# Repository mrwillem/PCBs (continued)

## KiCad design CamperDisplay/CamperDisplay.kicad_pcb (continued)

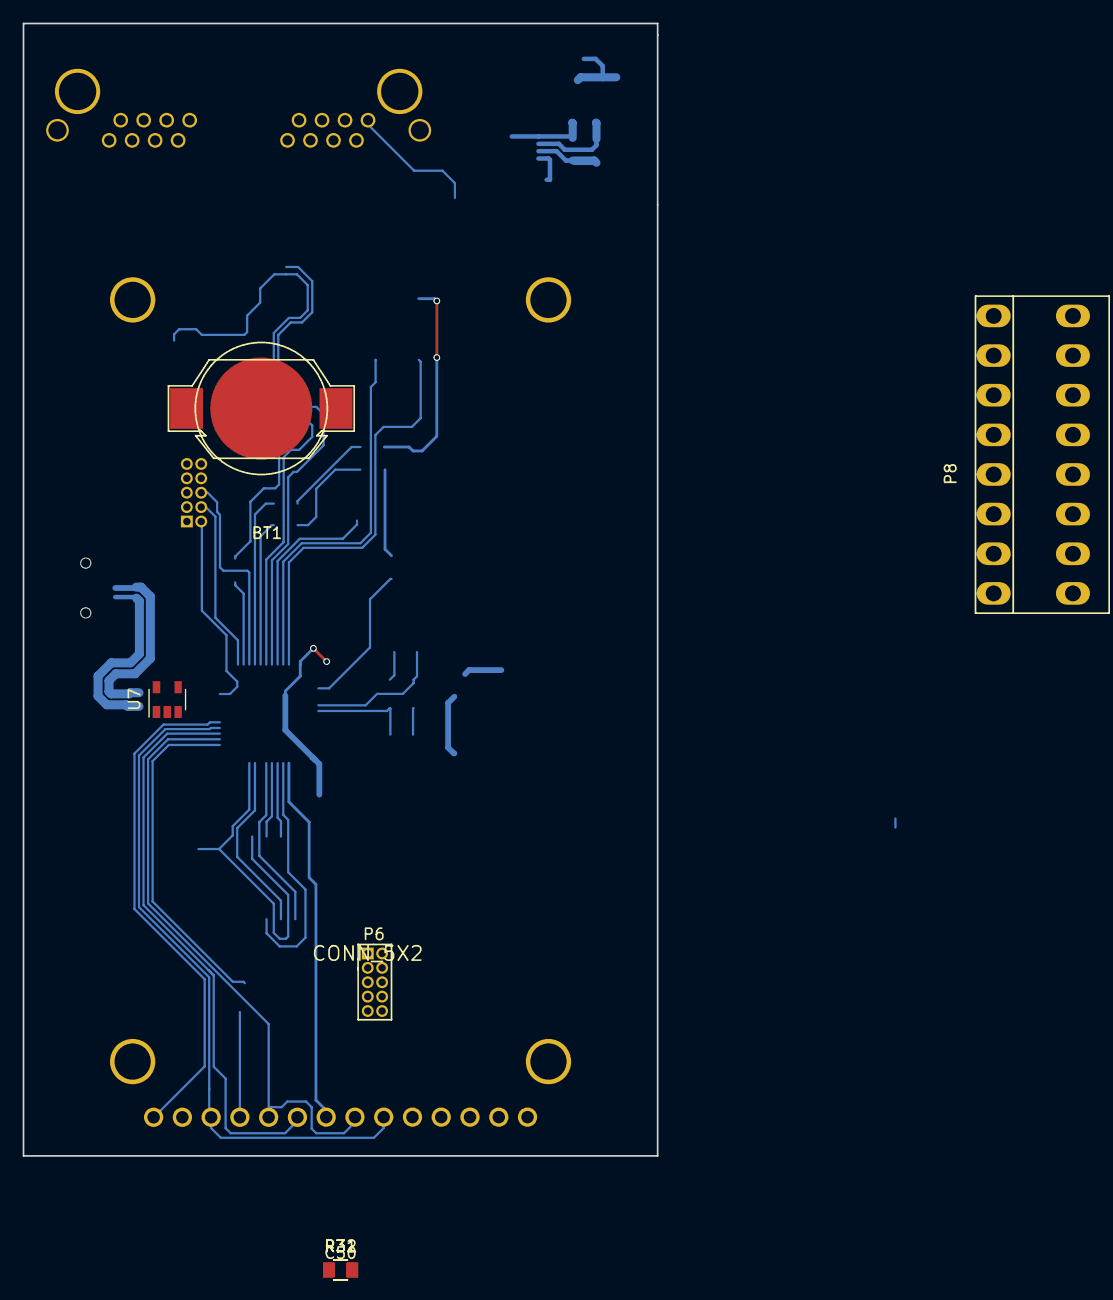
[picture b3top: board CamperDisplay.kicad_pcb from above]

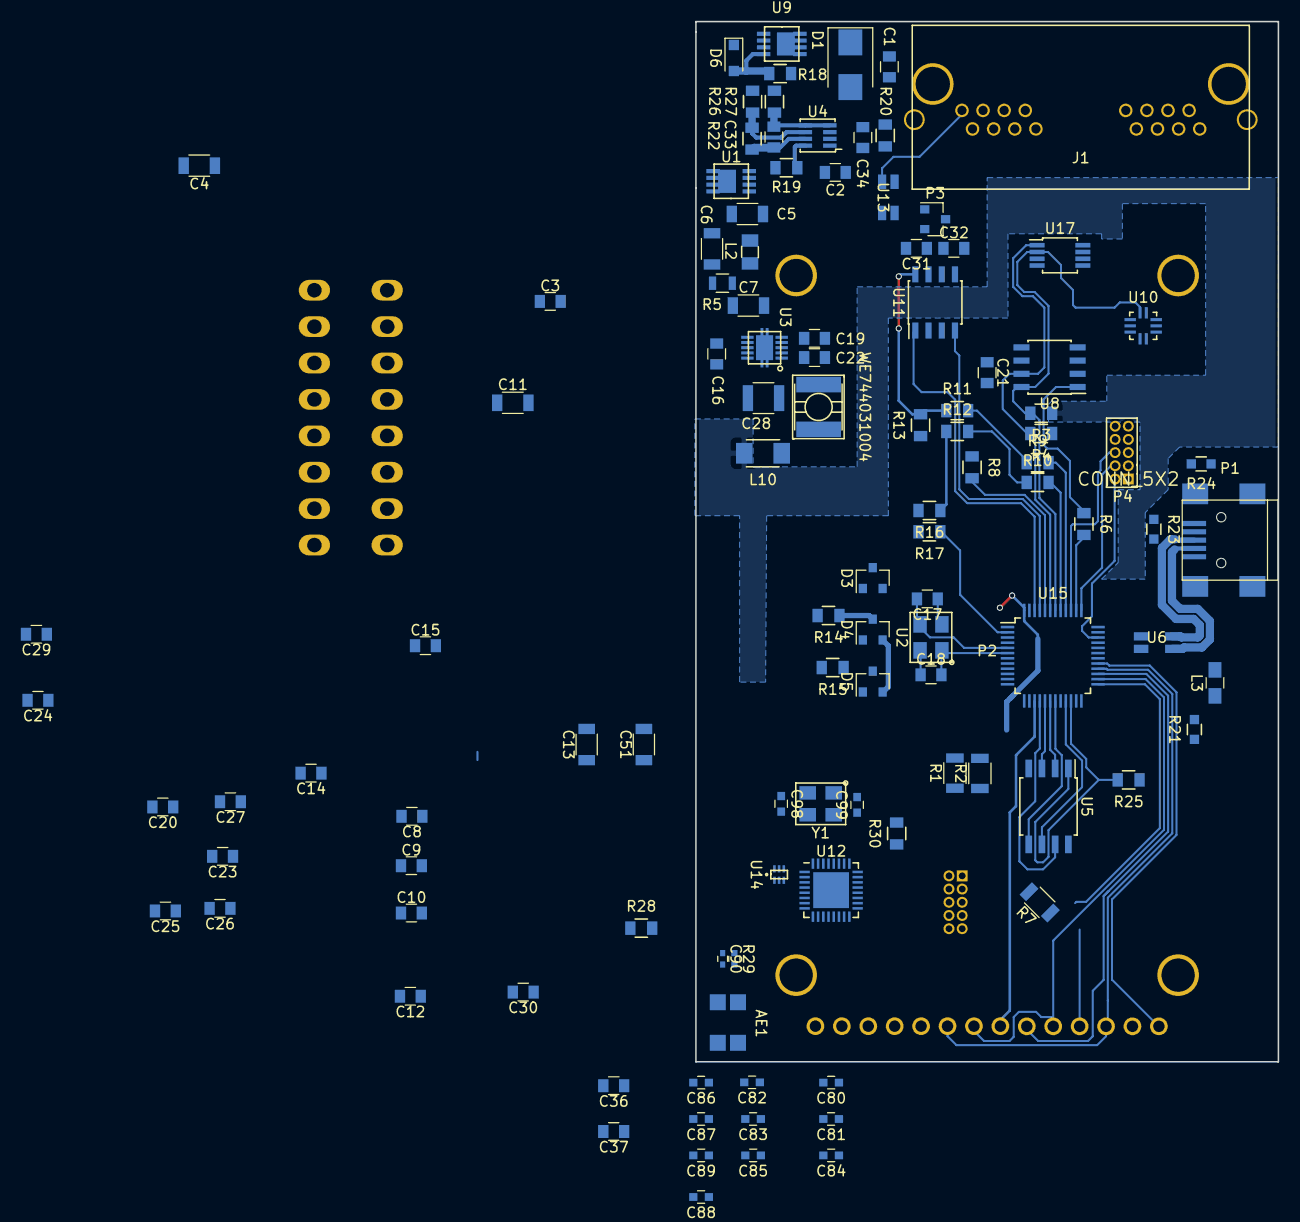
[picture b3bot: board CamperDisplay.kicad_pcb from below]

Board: 2 copper layers, 56.0 x 100.0 mm, 119 parts (112 on the bottom side), 91 nets.

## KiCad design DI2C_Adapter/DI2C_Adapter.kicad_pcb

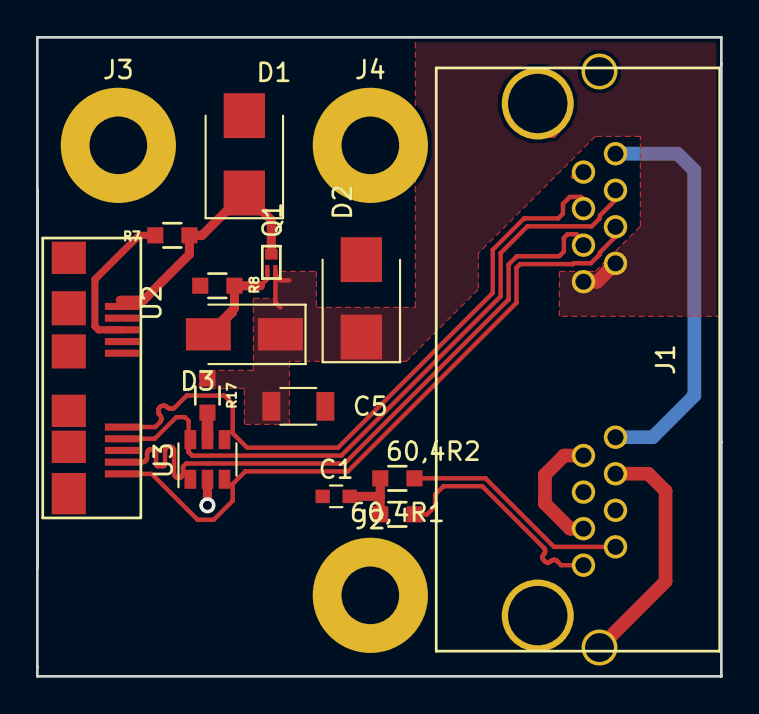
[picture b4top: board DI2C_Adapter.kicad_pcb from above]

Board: 2 copper layers, 38.0 x 35.5 mm, 17 parts (0 on the bottom side), 16 nets.

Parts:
60,4R1, 60,4R2: R; R_0603_HandSolder
C1: 4,7nF; C_0603
C5: 10uF; C_1206
D1: ATV06B5V0JB-HF; D_SMB
D2: 1SMB5913BT3G; D_SMB
D3: D; D_SMA
J1: RJHSE-5380-02; RJHSE538X-02-noled
J2, J3, J4: CONN_01X01; MountingHole_3.2mm_M3_Pad
Q1: DMP58D0LFB; X1-DFN1006-3
R7, R8: R; R_0603_HandSolder
R17: 0R0; R_0603_HandSolder
U2: Micro_USB3_GSB343133HR; USB_Micro-3_GSB343133HR
U3: WE824013; SOT-23-6

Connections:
+3V3: C5.1, D2.1, D3.1, J1.9, J1.10, Q1.2, R17.1
+12V: J1.8, J1.16
CANGND: C1.1, J1.3, J1.7
CANH: 60,4R2.2, J1.1
CANL: 60,4R1.1, J1.2
CANSHLD: J1.6, J1.17
GND: C5.2, D1.2, D2.2, J1.15, R8.1, U2.5, U2.8, U3.2
unnamed: 60,4R1.2, 60,4R2.1, C1.2
unnamed: D3.2, Q1.1, R8.2
unnamed: R7.2, U2.3
unnamed: R17.2, U3.5
SCL+: J1.13, U2.6, U3.4
SCL-: J1.14, U2.7, U3.6
SDA+: J1.12, U2.10, U3.3
SDA-: J1.11, U2.9, U3.1
VSRC: D1.1, Q1.3, R7.1, U2.1

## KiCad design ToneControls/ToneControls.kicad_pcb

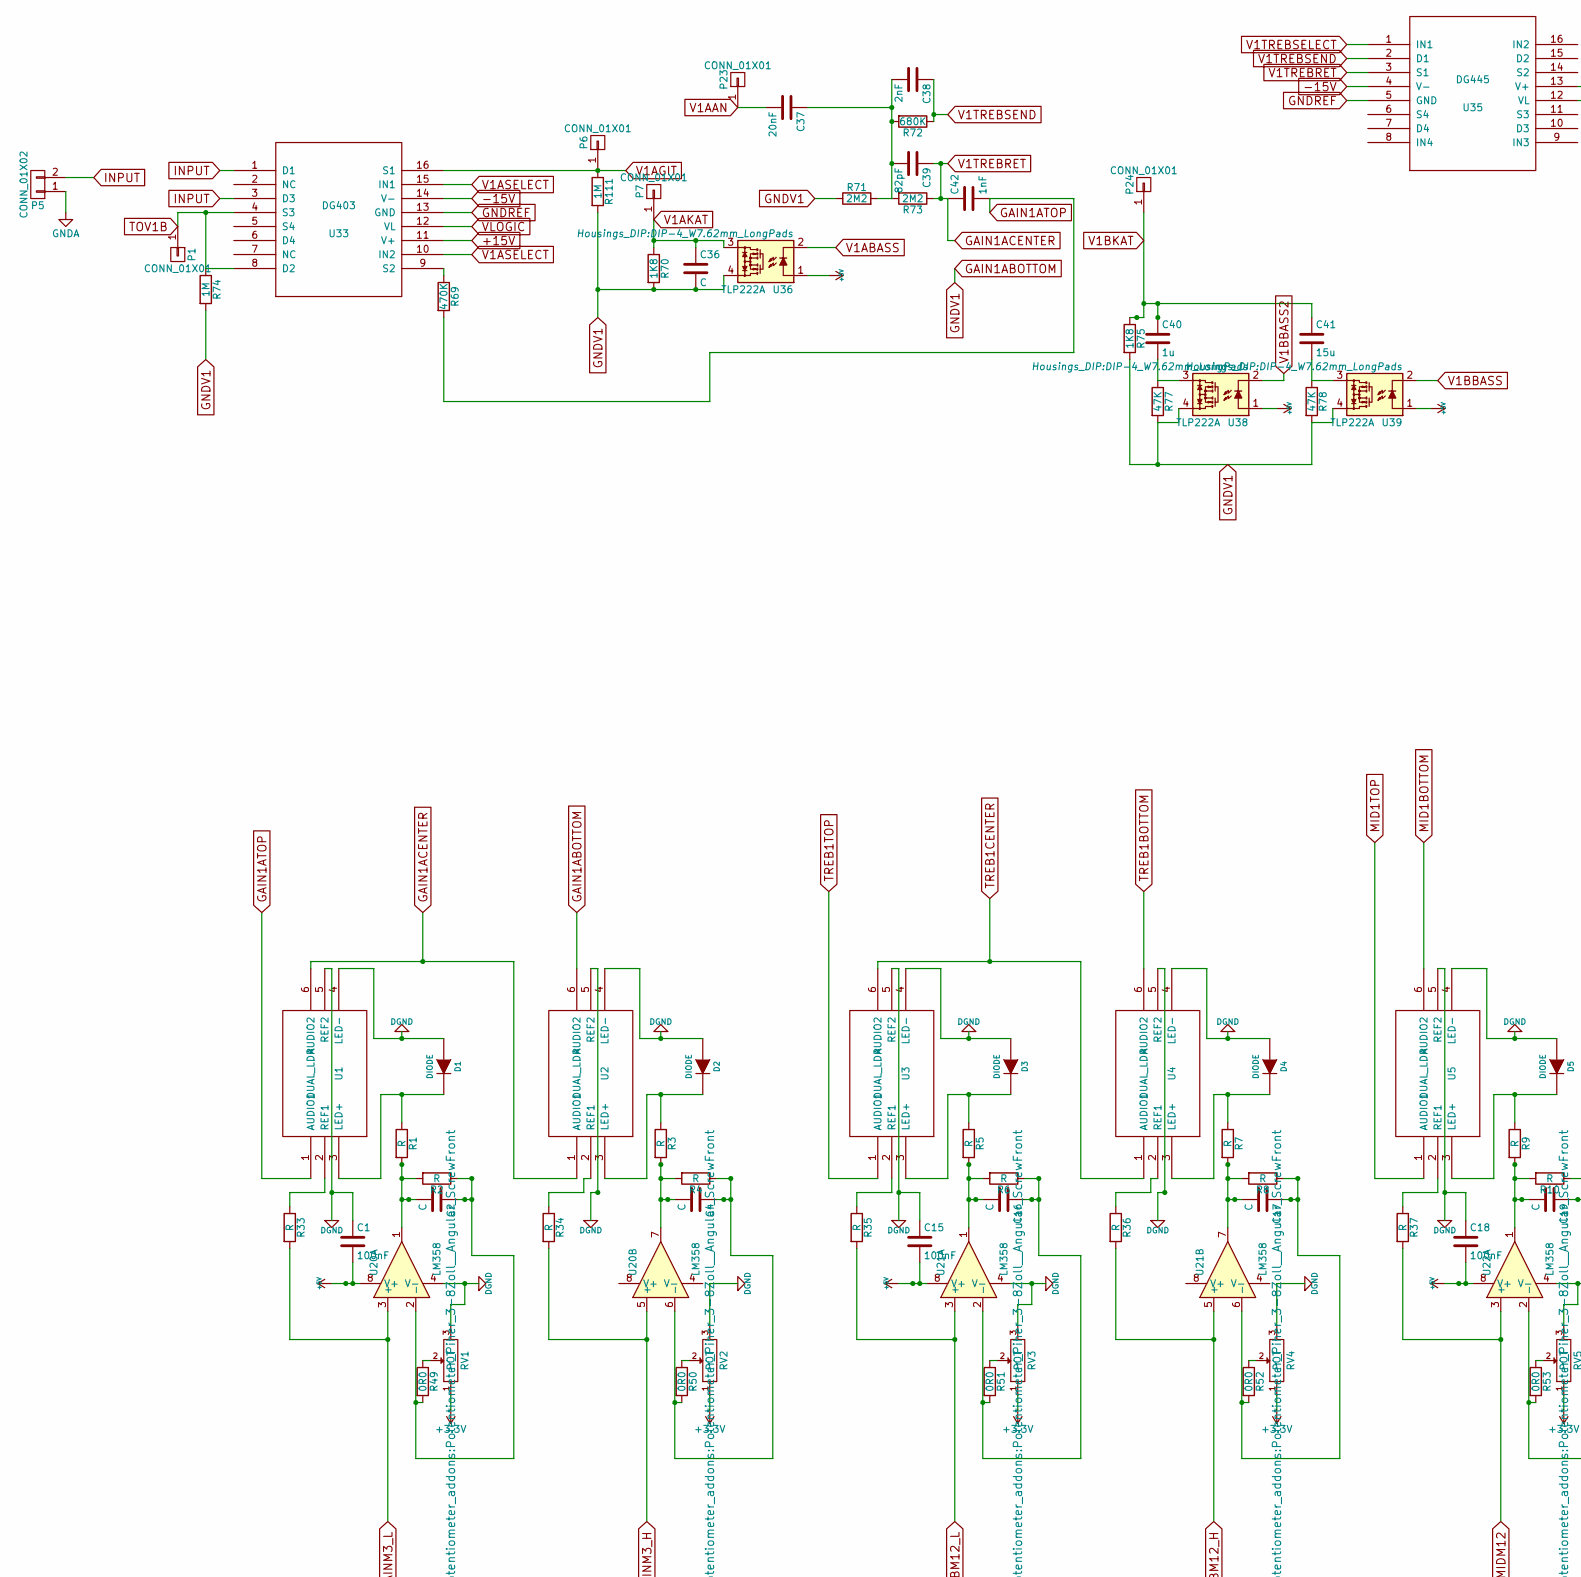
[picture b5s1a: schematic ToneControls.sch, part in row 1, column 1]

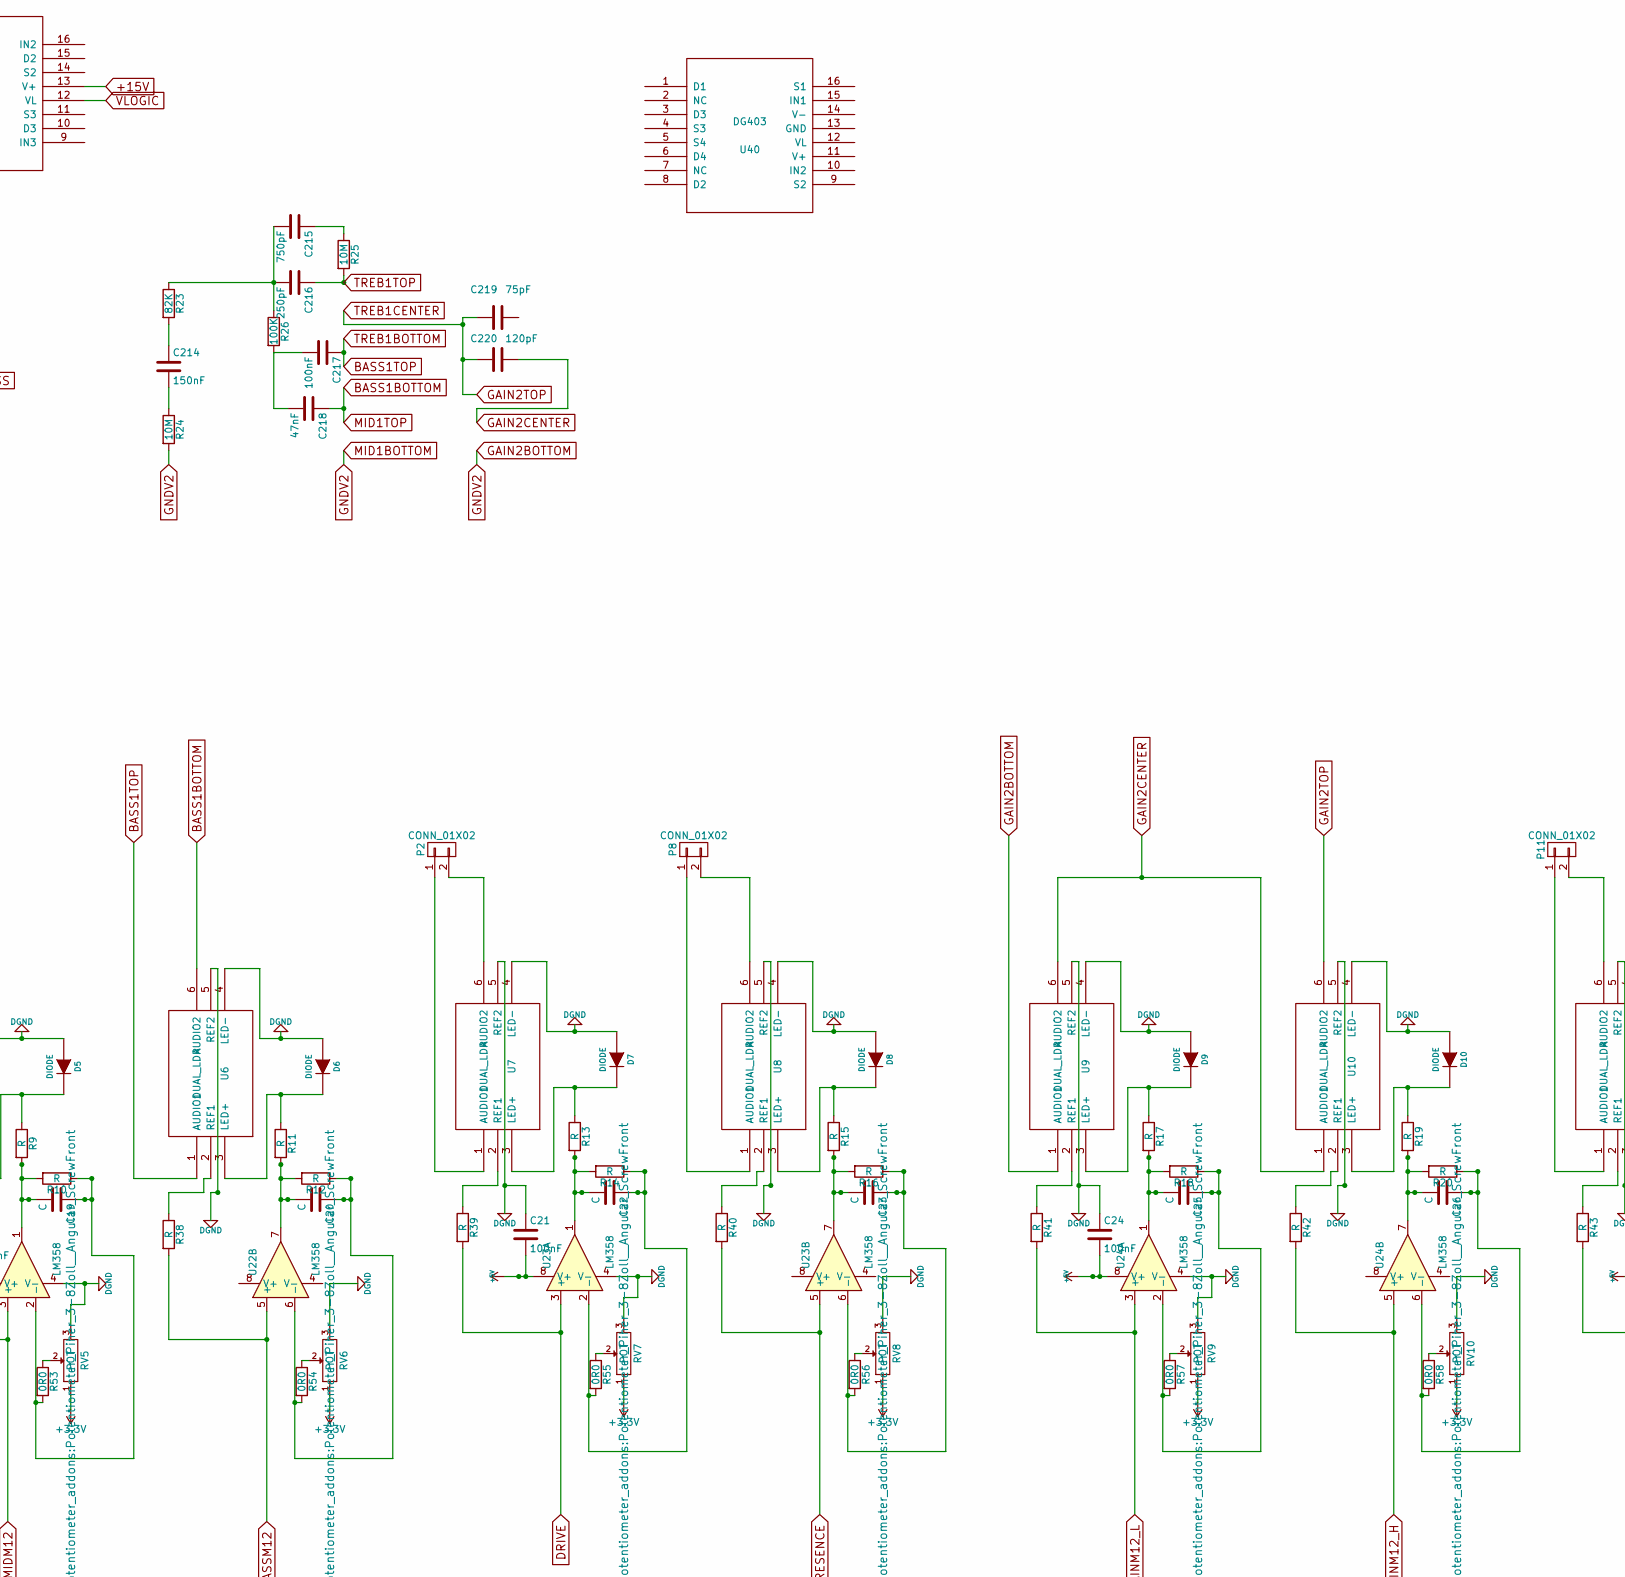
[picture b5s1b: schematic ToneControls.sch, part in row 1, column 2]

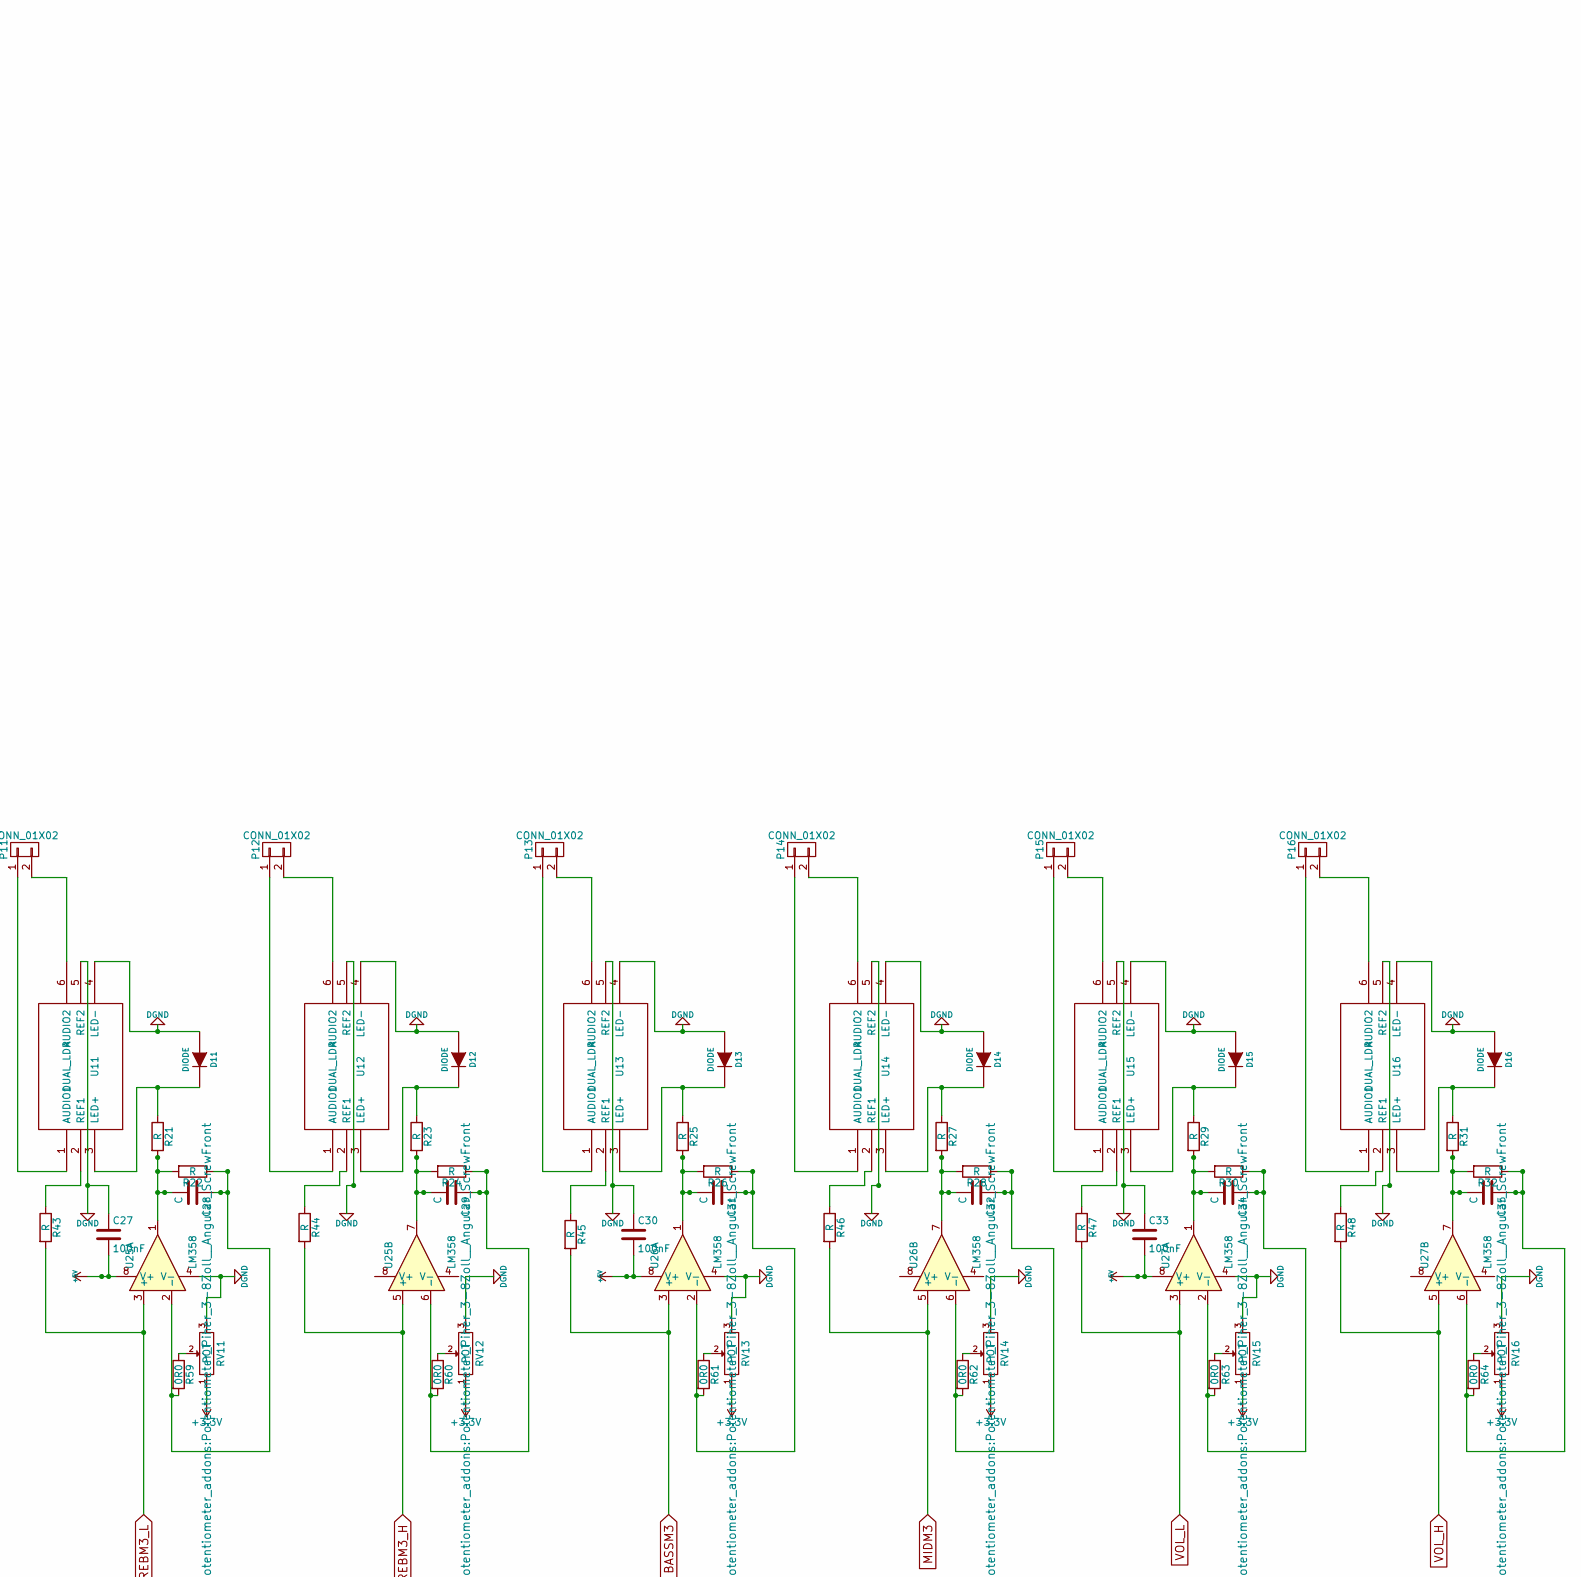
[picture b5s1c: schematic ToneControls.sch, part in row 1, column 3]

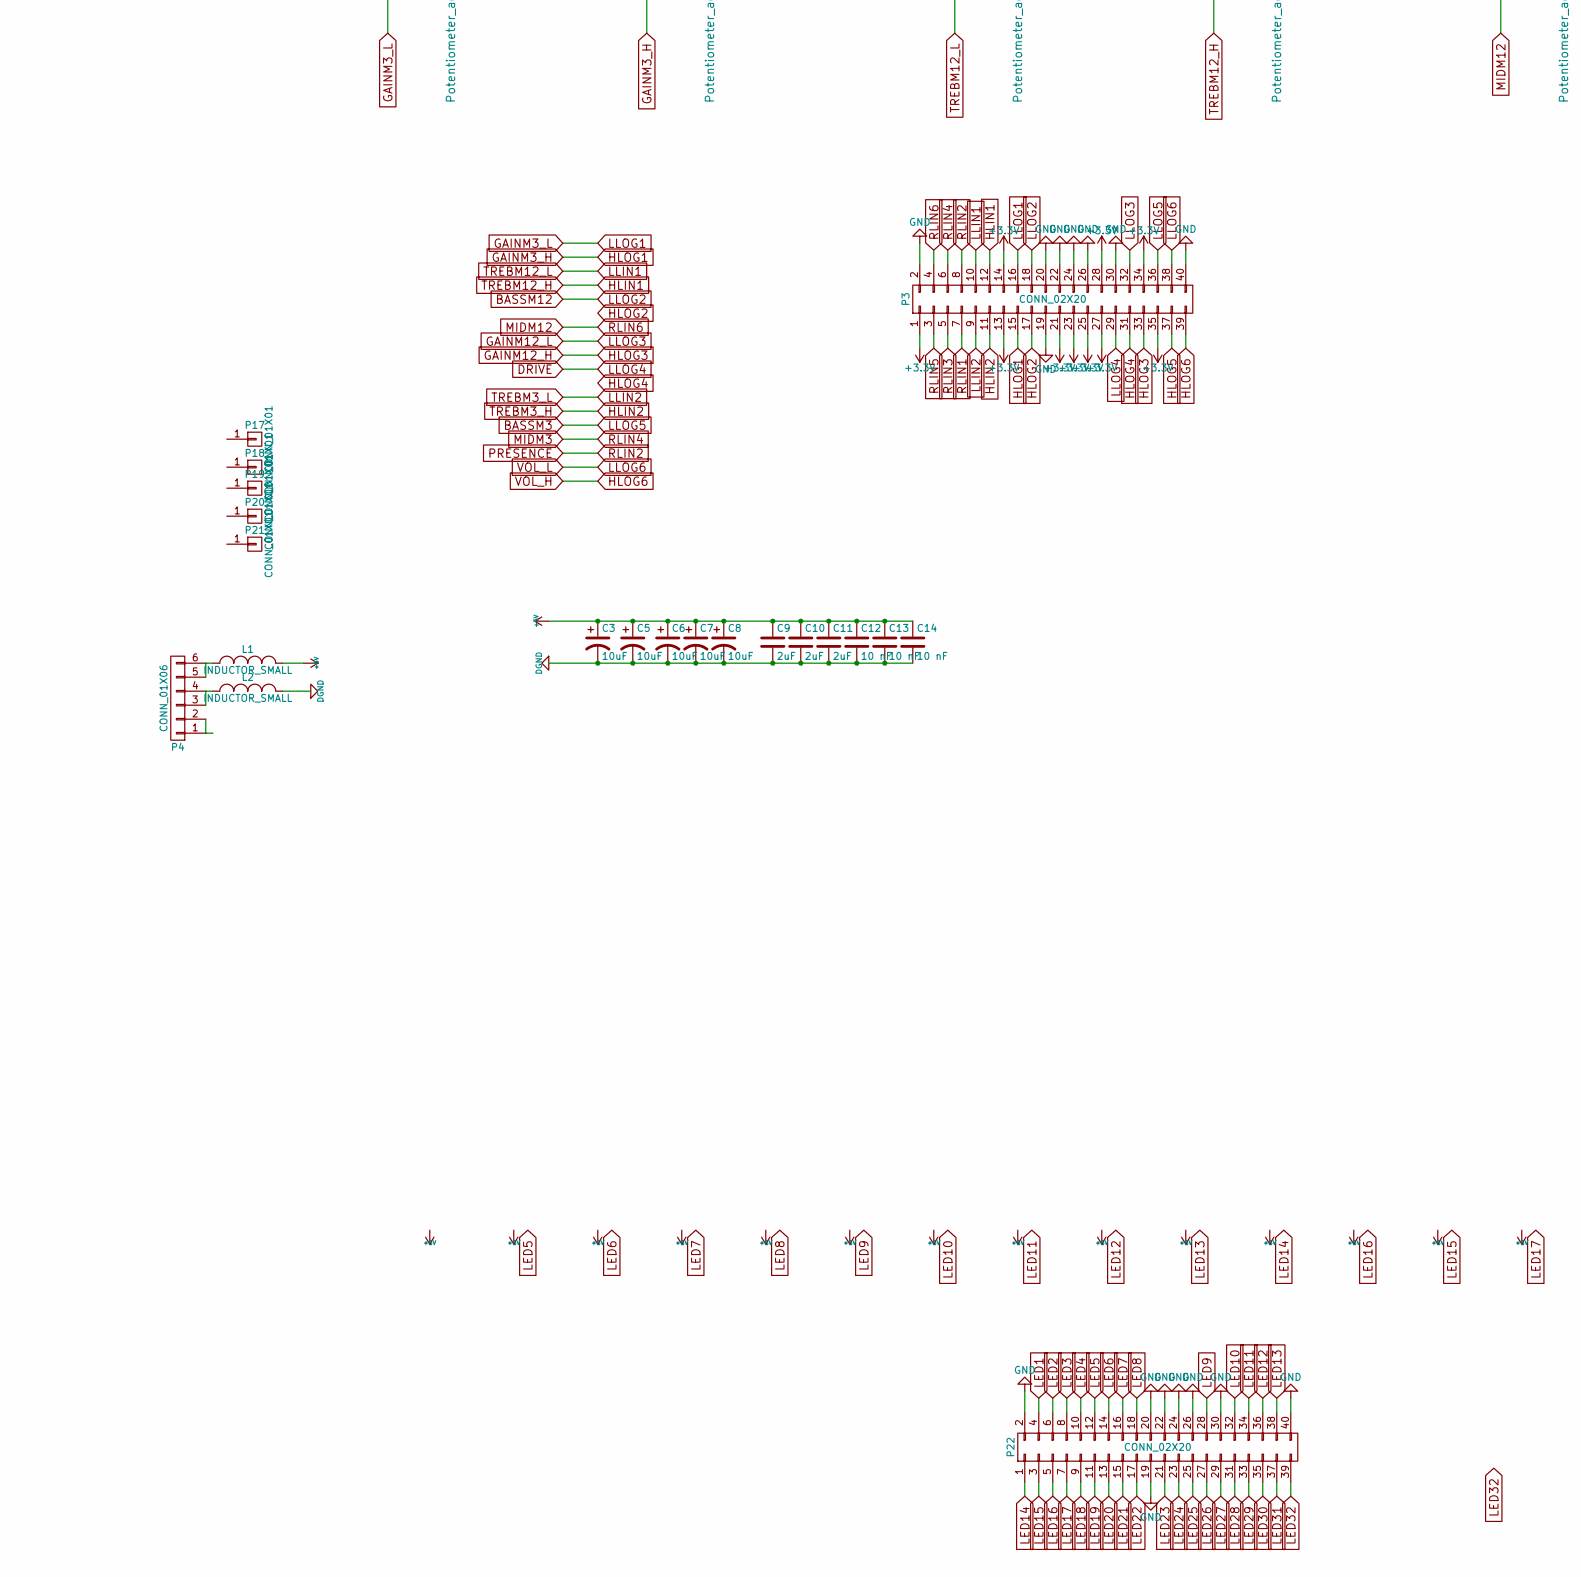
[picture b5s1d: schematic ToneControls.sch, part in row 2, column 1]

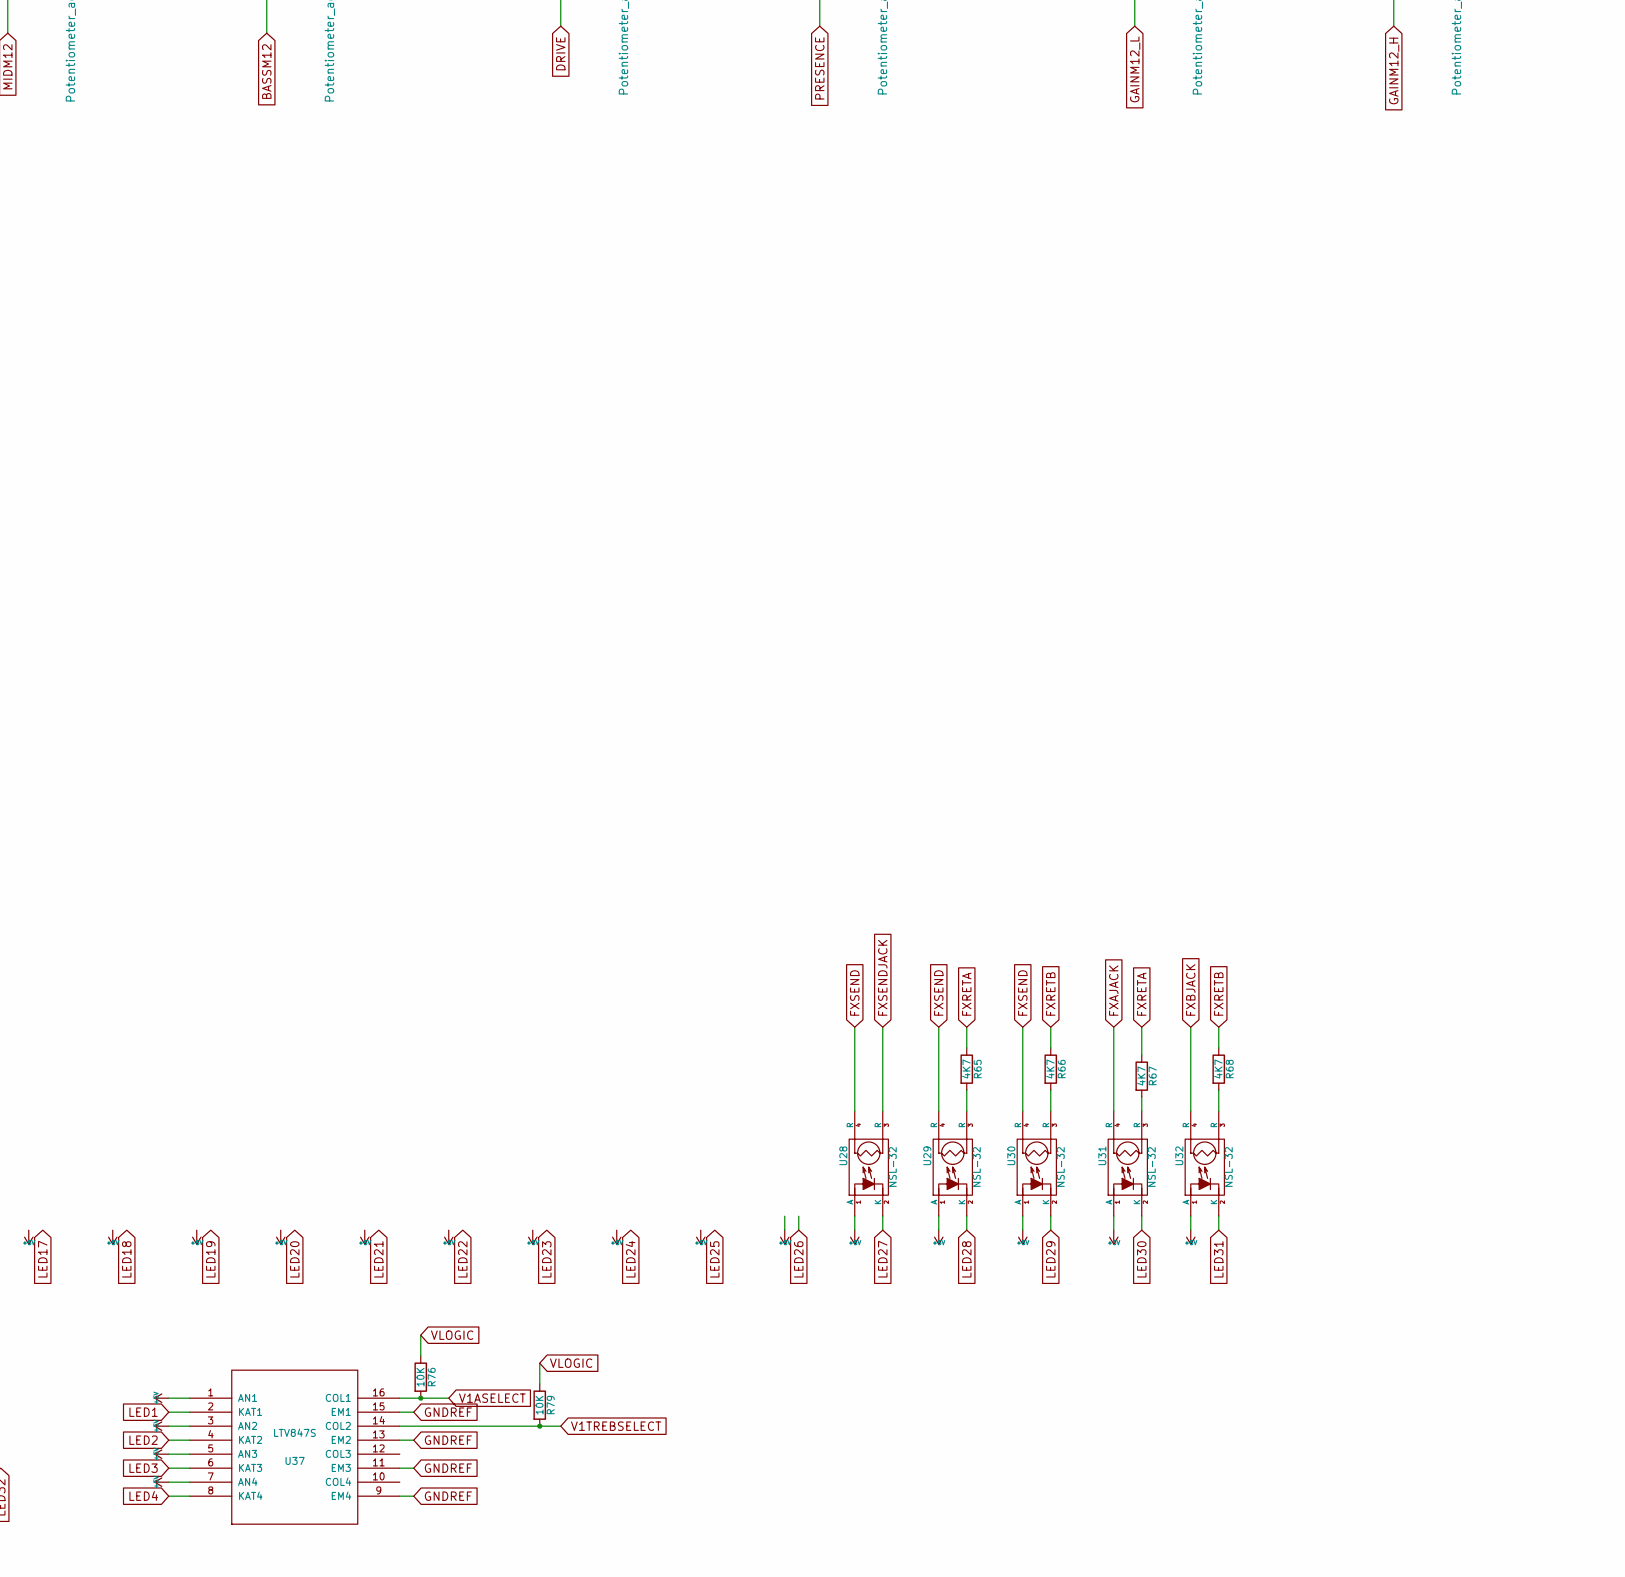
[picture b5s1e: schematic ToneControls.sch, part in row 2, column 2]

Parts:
C1, C15, C18, C21, C24, C27, C30, C33: 100nF; C_0805
C2, C4, C16, C17, C19, C20, C22, C23, C25, C26, C28, C29, C31, C32, C34, C35: C; C_0805
C3, C5, C6, C7, C8: 10uF; c_elec_4x5.8
C9, C10, C11: 2uF; C_0805
C12, C13, C14: 10 nF; C_0805
C36: C; C_Rect_L7_W2.5_P5
C37: 20nF; C_Rect_L7_W2.5_P5
C38: 2nF; C_Rect_L7_W2.5_P5
C39: 82pF; C_Rect_L7_W2.5_P5
C40: 1u; C_Rect_L7_W2.5_P5
C41: 15u; C_Rect_L7_W2.5_P5
C42: 1nF; C_Rect_L7_W2.5_P5
C214: 150nF
C215: 750pF
C216: 250pF
C217: 100nF
C218: 47nF
C219: 75pF
C220: 120pF
D1, D2, D3, D4, D5, D6, D7, D8, D9, D10, D11, D12, D13, D14, D15, D16: DIODE; SOD-323-Handsoldering
L1, L2: INDUCTOR_SMALL; C_0805_HandSoldering
P1, P6, P7, P23, P24: CONN_01X01; Pin_Header_Angled_1x01
P2, P5, P8, P11, P12, P13, P14, P15, P16: CONN_01X02; PINHEAD1-2
P3, P22: CONN_02X20; IDC_Header_Straight_40pins
P4: CONN_01X06; PINHEAD1-6
P17, P18, P19, P20, P21: CONN_01X01; hole
R1, R2, R3, R4, R5, R6, R7, R8, R9, R10, R11, R12, R13, R14, R15, R16, R17, R18, R19, R20, R21, R22, R23, R24, R25, R26, R27, R28, R29, R30, R31, R32, R33, R34, R35, R36, R37, R38, R39, R40, R41, R42, R43, R44, R45, R46, R47, R48: R; R_0805_HandSoldering
R49, R50, R51, R52, R53, R54, R55, R56, R57, R58, R59, R60, R61, R62, R63, R64: 0R0; R_1206
R65, R66, R67, R68: 4K7; R_0805_HandSoldering
R69: 470K; Resistor_Horizontal_RM7mm
R70, R75: 1K8; Resistor_Horizontal_RM7mm
R71, R73: 2M2; Resistor_Horizontal_RM7mm
R72: 680K; Resistor_Horizontal_RM7mm
R74, R111: 1M; Resistor_Horizontal_RM7mm
R76, R79: 10K; R_0805_HandSoldering
R77, R78: 47K; Resistor_Horizontal_RM7mm
RV1, RV2, RV3, RV4, RV5, RV6, RV7, RV8, RV9, RV10, RV11, RV12, RV13, RV14, RV15, RV16: POT; Potentiometer_Piher_3-8Zoll__Angular_ScrewFront
U1, U2, U3, U4, U5, U6, U7, U8, U9, U10, U11, U12, U13, U14, U15, U16: DUAL_LDR; DIP-6_W7.62mm
U20, U21, U22, U23, U24, U25, U26, U27: LM358; SOIC-8_3.9x4.9mm_Pitch1.27mm
U28, U29, U30, U31, U32: NSL-32; Optoisolator_NSL-32
U33, U40: DG403; SOIC-16_3.9x9.9mm_Pitch1.27mm
U35: DG445; SOIC-16_3.9x9.9mm_Pitch1.27mm
U36, U38, U39: TLP222A; DIP-4_W7.62mm_LongPads
U37: LTV847S; DIP-16_W7.62mm_LongPads

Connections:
+3V3: P3.1, P3.13, P3.14, P3.21, P3.23, P3.25, P3.27, P3.28, P3.34, P3.35, RV1.1, RV2.1, RV3.1, RV4.1, RV5.1, RV6.1, RV7.1, RV8.1, RV9.1, RV10.1, RV11.1, RV12.1, RV13.1, RV14.1, RV15.1, RV16.1
+5V: C1.2, C3.1, C5.1, C6.1, C7.1, C8.1, C9.1, C10.1, C11.1, C12.1, C13.1, C14.1, C15.2, C18.2, C21.2, C24.2, C27.2, C30.2, C33.2, L1.2, U20.8 (V+), U21.8 (V+), U22.8 (V+), U23.8 (V+), U24.8 (V+), U25.8 (V+), U26.8 (V+), U27.8 (V+), U28.1 (A), U29.1 (A), U30.1 (A), U31.1 (A), U32.1 (A), U36.1, U37.1 (AN1), U37.3 (AN2), U37.5 (AN3), U37.7 (AN4), U38.1, U39.1
+15V: U33.11 (V+), U35.13 (V+)
-15V: U33.14 (V-), U35.4 (V-)
BASSM3: P3.36, R45.2, U26.3 (+)
BASSM12: P3.18, R38.2, U22.5 (+)
DGND: C1.1, C3.2, C5.2, C6.2, C7.2, C8.2, C9.2, C10.2, C11.2, C12.2, C13.2, C14.2, C15.1, C18.1, C21.1, C24.1, C27.1, C30.1, C33.1, D1.1 (A), D2.1 (A), D3.1 (A), D4.1 (A), D5.1 (A), D6.1 (A), D7.1 (A), D8.1 (A), D9.1 (A), D10.1 (A), D11.1 (A), D12.1 (A), D13.1 (A), D14.1 (A), D15.1 (A), D16.1 (A), L2.2, RV1.3, RV2.3, RV3.3, RV4.3, RV5.3, RV6.3, RV7.3, RV8.3, RV9.3, RV10.3, RV11.3, RV12.3, RV13.3, RV14.3, RV15.3, RV16.3, U1.4 (LED-), U1.5 (REF2), U2.4 (LED-), U2.5 (REF2), U3.4 (LED-), U3.5 (REF2), U4.4 (LED-), U4.5 (REF2), U5.4 (LED-), U5.5 (REF2), U6.4 (LED-), U6.5 (REF2), U7.4 (LED-), U7.5 (REF2), U8.4 (LED-), U8.5 (REF2), U9.4 (LED-), U9.5 (REF2), U10.4 (LED-), U10.5 (REF2), U11.4 (LED-), U11.5 (REF2), U12.4 (LED-), U12.5 (REF2), U13.4 (LED-), U13.5 (REF2), U14.4 (LED-), U14.5 (REF2), U15.4 (LED-), U15.5 (REF2), U16.4 (LED-), U16.5 (REF2), U20.4 (V-), U21.4 (V-), U22.4 (V-), U23.4 (V-), U24.4 (V-), U25.4 (V-), U26.4 (V-), U27.4 (V-)
DRIVE: P3.29, R39.2, U23.3 (+)
FXAJACK: U31.4 (R)
FXBJACK: U32.4 (R)
FXRETA: R65.1, R67.1
FXRETB: R66.1, R68.1
FXSEND: U28.4 (R), U29.4 (R), U30.4 (R)
FXSENDJACK: U28.3 (R)
GAIN1ABOTTOM: C36.2, R70.2, R71.1, R74.2, R75.2, R77.2, R78.2, R111.2, U2.6 (AUDIO2), U36.4, U38.4, U39.4
GAIN1ACENTER: C39.1, C42.1, R73.1, U1.6 (AUDIO2), U2.1 (AUDIO1), U35.3 (S1)
GAIN1ATOP: C42.2, R69.2, U1.1 (AUDIO1)
GAINM3_H: P3.15, R34.2, U20.5 (+)
GAINM3_L: P3.16, R33.2, U20.3 (+)
GAINM12_H: P3.33, R42.2, U24.5 (+)
GAINM12_L: P3.32, R41.2, U24.3 (+)
GND: P3.2, P3.19, P3.20, P3.22, P3.24, P3.26, P3.30, P3.40, P22.2, P22.19, P22.20, P22.22, P22.24, P22.26, P22.30, P22.40
GNDA: P5.1
GNDREF: U33.13 (GND), U35.5 (GND), U37.9 (EM4), U37.11 (EM3), U37.13 (EM2), U37.15 (EM1)
HLIN1: P3.12, R36.2, U21.5 (+)
HLIN2: P3.11, R44.2, U25.5 (+)
HLOG2: P3.17
HLOG4: P3.31
HLOG5: P3.37
HLOG6: P3.39, R48.2, U27.5 (+)
INPUT: P5.2, U33.1 (D1), U33.3 (D3)
LED1: P22.4, U37.2 (KAT1)
LED2: P22.6, U37.4 (KAT2)
LED3: P22.8, U37.6 (KAT3)
LED4: P22.10, U37.8 (KAT4)
LED5: P22.12
LED6: P22.14
LED7: P22.16
LED8: P22.18
LED9: P22.28
LED10: P22.32
LED11: P22.34
LED12: P22.36
LED13: P22.38
LED14: P22.1
LED15: P22.3
LED16: P22.5
LED17: P22.7
LED18: P22.9
LED19: P22.11
LED20: P22.13
LED21: P22.15
LED22: P22.17
LED23: P22.21
LED24: P22.23
LED25: P22.25
LED26: P22.27
LED27: P22.29, U28.2 (K)
LED28: P22.31, U29.2 (K)
LED29: P22.33, U30.2 (K)
LED30: P22.35, U31.2 (K)
LED31: P22.37, U32.2 (K)
LED32: P22.39
LLIN1: P3.10, R35.2, U21.3 (+)
LLIN2: P3.9, R43.2, U25.3 (+)
LLOG6: P3.38, R47.2, U27.3 (+)
MIDM3: P3.6, R46.2, U26.5 (+)
MIDM12: P3.4, R37.2, U22.3 (+)
unnamed: C2.1, R2.1, R49.2, U20.2 (-)
unnamed: C2.2, R1.2, R2.2, U20.1
unnamed: C4.1, R4.1, R50.2, U20.6 (-)
unnamed: C4.2, R3.2, R4.2, U20.7
unnamed: C16.1, R6.1, R51.2, U21.2 (-)
unnamed: C16.2, R5.2, R6.2, U21.1
unnamed: C17.1, R8.1, R52.2, U21.6 (-)
unnamed: C17.2, R7.2, R8.2, U21.7
unnamed: C19.1, R10.1, R53.2, U22.2 (-)
unnamed: C19.2, R9.2, R10.2, U22.1
unnamed: C20.1, R12.1, R54.2, U22.6 (-)
unnamed: C20.2, R11.2, R12.2, U22.7
unnamed: C22.1, R14.1, R55.2, U23.2 (-)
unnamed: C22.2, R13.2, R14.2, U23.1
unnamed: C23.1, R16.1, R56.2, U23.6 (-)
unnamed: C23.2, R15.2, R16.2, U23.7
unnamed: C25.1, R18.1, R57.2, U24.2 (-)
unnamed: C25.2, R17.2, R18.2, U24.1
unnamed: C26.1, R20.1, R58.2, U24.6 (-)
unnamed: C26.2, R19.2, R20.2, U24.7
unnamed: C28.1, R22.1, R59.2, U25.2 (-)
unnamed: C28.2, R21.2, R22.2, U25.1
unnamed: C29.1, C214.2, R24.1, R60.2, U25.6 (-)
unnamed: C32.1, R28.1, R62.2, U26.6 (-)
unnamed: C32.2, R27.2, R28.2, U26.7
unnamed: C34.1, R30.1, R63.2, U27.2 (-)
unnamed: C34.2, R29.2, R30.2, U27.1
unnamed: C35.1, R32.1, R64.2, U27.6 (-)
unnamed: C35.2, R31.2, R32.2, U27.7
unnamed: C37.1, C38.2, C39.2, R71.2, R72.2, R73.2
unnamed: C40.2, R77.1, U38.3
unnamed: C41.2, R78.1, U39.3
unnamed: D1.2 (K), R1.1, U1.3 (LED+)
unnamed: D2.2 (K), R3.1, U2.3 (LED+)
unnamed: D3.2 (K), R5.1, U3.3 (LED+)
unnamed: D4.2 (K), R7.1, U4.3 (LED+)
unnamed: D5.2 (K), R9.1, U5.3 (LED+)
unnamed: D6.2 (K), R11.1, U6.3 (LED+)
unnamed: D7.2 (K), R13.1, U7.3 (LED+)
unnamed: D8.2 (K), R15.1, U8.3 (LED+)
unnamed: D9.2 (K), R17.1, U9.3 (LED+)
unnamed: D10.2 (K), R19.1, U10.3 (LED+)
unnamed: D11.2 (K), R21.1, U11.3 (LED+)
unnamed: C215.1, D13.2 (K), R25.1, U13.3 (LED+)
unnamed: D14.2 (K), R27.1, U14.3 (LED+)
unnamed: D15.2 (K), R29.1, U15.3 (LED+)
unnamed: D16.2 (K), R31.1, U16.3 (LED+)
unnamed: L1.1, P4.5, P4.6
unnamed: L2.1, P4.3, P4.4
unnamed: P2.1, U7.1 (AUDIO1)
unnamed: P2.2, U7.6 (AUDIO2)
unnamed: P4.1, P4.2
unnamed: P8.1, U8.1 (AUDIO1)
unnamed: P8.2, U8.6 (AUDIO2)
unnamed: P11.1, U11.1 (AUDIO1)
unnamed: P11.2, U11.6 (AUDIO2)
unnamed: P12.1, U12.1 (AUDIO1)
unnamed: P12.2, U12.6 (AUDIO2)
unnamed: P13.1, U13.1 (AUDIO1)
unnamed: P13.2, U13.6 (AUDIO2)
unnamed: P14.1, U14.1 (AUDIO1)
unnamed: P14.2, U14.6 (AUDIO2)
unnamed: P15.1, U15.1 (AUDIO1)
unnamed: P15.2, U15.6 (AUDIO2)
unnamed: P16.1, U16.1 (AUDIO1)
unnamed: P16.2, U16.6 (AUDIO2)
unnamed: R33.1, U1.2 (REF1)
unnamed: R34.1, U2.2 (REF1)
unnamed: R35.1, U3.2 (REF1)
unnamed: R36.1, U4.2 (REF1)
unnamed: R37.1, U5.2 (REF1)
unnamed: R38.1, U6.2 (REF1)
unnamed: R39.1, U7.2 (REF1)
unnamed: R40.1, U8.2 (REF1)
unnamed: R41.1, U9.2 (REF1)
unnamed: R42.1, U10.2 (REF1)
unnamed: R43.1, U11.2 (REF1)
unnamed: R44.1, U12.2 (REF1)
unnamed: R45.1, U13.2 (REF1)
unnamed: R46.1, U14.2 (REF1)
unnamed: R47.1, U15.2 (REF1)
unnamed: R48.1, U16.2 (REF1)
unnamed: R49.1, RV1.2
unnamed: R50.1, RV2.2
unnamed: R51.1, RV3.2
unnamed: R52.1, RV4.2
unnamed: R53.1, RV5.2
unnamed: R54.1, RV6.2
unnamed: R55.1, RV7.2
unnamed: R56.1, RV8.2
unnamed: R57.1, RV9.2
unnamed: R58.1, RV10.2
unnamed: R59.1, RV11.2
unnamed: R60.1, RV12.2
unnamed: R61.1, RV13.2
unnamed: R62.1, RV14.2
unnamed: R63.1, RV15.2
unnamed: R64.1, RV16.2
unnamed: R65.2, U29.3 (R)
unnamed: R66.2, U30.3 (R)
unnamed: R67.2, U31.3 (R)
unnamed: R68.2, U32.3 (R)
unnamed: R69.1, U33.9 (S2)
PRESENCE: P3.8, R40.2, U23.5 (+)
RLIN1: P3.7
RLIN3: P3.5
RLIN5: P3.3
TOV1B: P1.1, R74.1, U33.4 (S3), U33.8 (D2)
V1AAN: C37.2, P23.1
V1ABASS: U36.2
V1AGIT: P6.1, R111.1, U33.16 (S1)
V1AKAT: C36.1, P7.1, R70.1, U36.3
V1ASELECT: R76.2, U33.10 (IN2), U33.15 (IN1), U37.16 (COL1)
V1BBASS: U39.2
V1BBASS2: U38.2
V1BKAT: C40.1, C41.1, P24.1, R75.1
V1TREBSELECT: R79.2, U35.1 (IN1), U37.14 (COL2)
V1TREBSEND: C38.1, R72.1, U35.2 (D1)
VLOGIC: R76.1, R79.1, U33.12 (VL), U35.12 (VL)

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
